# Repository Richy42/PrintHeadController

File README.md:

# PrintHeadController
A 3D printer controller board

Inspired by the possibility of Klipper 3D printer firmware (https://www.klipper3d.org/ ) that allows to have several I/O controller boards, PrintHeadController is a small board intended to be mounted on the moving print head assembly.

This reduces the cabling effort significantly as only power supply and USB is needed.

PrintHeadController has the following features:
* Based on the RP2040 MCU (the one that is used on the Raspberry PI Pico), so it is supported by the Klipper firmware out of the box
* Single socket for a stepper driver module e.g. DRV8825, various TMC variants
* Supports the SPI configuration of TMC drivers
* 12 V and 24 V capable
* 4 Digital inputs
* 4 MOSFET outputs (e.g. hotend heater, fans)
* 4 Thermistor inputs
* BLTouch support
* Debug pins accessible
* Accelerometer ADXL245 optional on board

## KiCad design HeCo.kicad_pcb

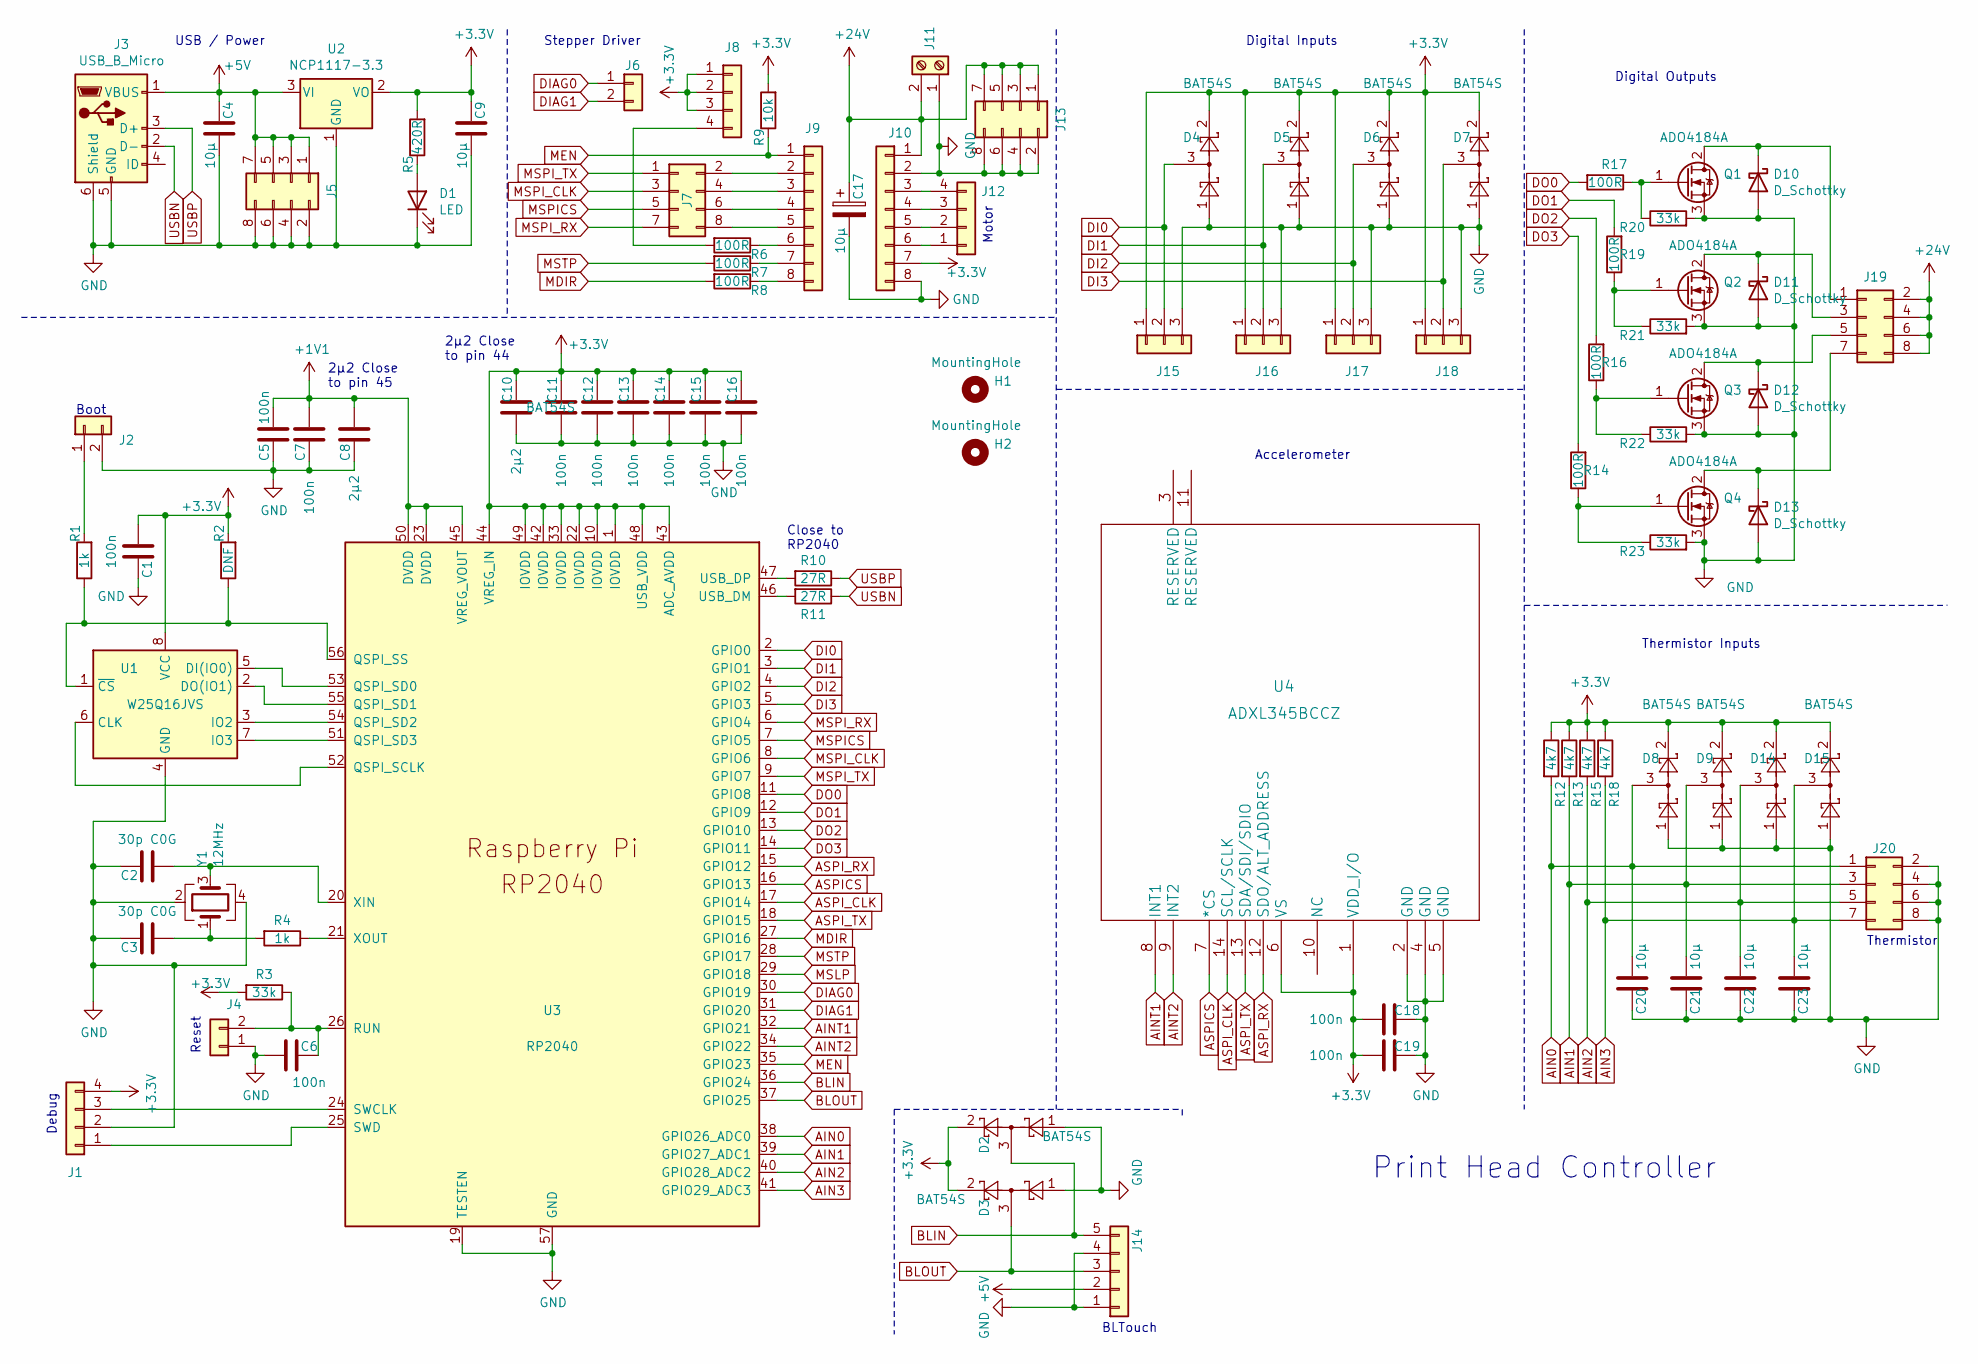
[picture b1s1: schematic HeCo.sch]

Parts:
C1, C5, C6, C7, C11, C12, C13, C14, C15, C16, C18, C19: 100n; C_0603_1608Metric
C2, C3: 30p C0G; C_0603_1608Metric
C4, C9, C20, C21, C22, C23: 10µ; C_0603_1608Metric
C8, C10: 2µ2; C_0603_1608Metric
C17: 10µ; CP_Elec_4x3
D1: LED; LED_0603_1608Metric
D2, D3, D4, D5, D6, D7, D8, D9, D14, D15: BAT54S; SOT-23
D10, D11, D12, D13: D_Schottky; D_0603_1608Metric
H1, H2: MountingHole; MountingHole_3.2mm_M3
J1, J8, J12: Conn_01x04; PinHeader_1x04_P2.54mm_Vertical
J2, J4: Conn_01x02; PinHeader_1x02_P2.54mm_Vertical
J3: USB_B_Micro; USB_Micro-B_Molex_47346-0001
J5, J7, J13, J19, J20: Conn_02x04_Odd_Even; PinHeader_2x04_P2.54mm_Vertical
J6: Conn_01x02; PinSocket_1x02_P2.54mm_Vertical
J9, J10: Conn_01x08; PinSocket_1x08_P2.54mm_Vertical
J11: Screw_Terminal_01x02; PhoenixContact_MSTBVA_2,5_2-G-5,08_1x02_P5.08mm_Vertical
J14: Conn_01x05; PinHeader_1x05_P2.54mm_Vertical
J15, J16, J17, J18: Conn_01x03; PinHeader_1x03_P2.54mm_Vertical
Q1, Q2, Q3, Q4: ADO4184A; TO-252-2
R1, R4: 1k; R_0603_1608Metric
R2: DNF; R_0603_1608Metric
R3, R20, R21, R22, R23: 33k; R_0603_1608Metric
R5: 420R; R_0603_1608Metric
R6, R7, R8, R14, R16, R17, R19: 100R; R_0603_1608Metric
R9: 10k; R_0603_1608Metric
R10, R11: 27R; R_0603_1608Metric
R12, R13, R15, R18: 4k7; R_0603_1608Metric
U1: W25Q16JVS; SOIC-8_5.23x5.23mm_P1.27mm
U2: NCP1117-3.3; SOT-223-3_TabPin2
U3: RP2040; RP2040-QFN-56
U4: ADXL345BCCZ
Y1: 12MHz; Crystal_SMD_3225-4Pin_3.2x2.5mm

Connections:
+1V1: C5.1, C7.1, C8.1, U3.23 (DVDD), U3.45 (VREG_VOUT), U3.50 (DVDD)
+3V3: C1.1, C9.1, C10.1, C11.1, C12.1, C13.1, C14.1, C15.1, C16.1, C18.2, C19.2, D2.2, D3.2, D4.2, D5.2, D6.2, D7.2, D8.2, D9.2, D14.2, D15.2, J1.4, J8.1, J8.2, J8.3, J10.7, J15.1, J16.1, J17.1, J18.1, R2.2, R3.2, R5.2, R9.2, R12.1, R13.1, R15.1, R18.1, U1.8 (VCC), U2.2 (VO), U3.1 (IOVDD), U3.10 (IOVDD), U3.22 (IOVDD), U3.33 (IOVDD), U3.42 (IOVDD), U3.43 (ADC_AVDD), U3.44 (VREG_IN), U3.48 (USB_VDD), U3.49 (IOVDD), U4.1 (VDD_I/O), U4.6 (VS)
+5V: C4.1, J3.1 (VBUS), J5.1, J5.3, J5.5, J5.7, J14.2, U2.3 (VI)
+24V: C17.1, J10.1, J11.2, J13.1, J13.3, J13.5, J13.7, J19.2, J19.4, J19.6, J19.8
AIN0: C20.1, D8.3, J20.1, R12.2, U3.38 (GPIO26_ADC0)
AIN1: C21.1, D9.3, J20.3, R13.2, U3.39 (GPIO27_ADC1)
AIN2: C22.1, D14.3, J20.5, R15.2, U3.40 (GPIO28_ADC2)
AIN3: C23.1, D15.3, J20.7, R18.2, U3.41 (GPIO29_ADC3)
AINT1: U3.32 (GPIO21), U4.8 (INT1)
AINT2: U3.34 (GPIO22), U4.9 (INT2)
ASPICS: U3.16 (GPIO13), U4.7 (*CS)
ASPI_CLK: U3.17 (GPIO14), U4.14 (SCL/SCLK)
ASPI_RX: U3.15 (GPIO12), U4.12 (SDO/ALT_ADDRESS)
ASPI_TX: U3.18 (GPIO15), U4.13 (SDA/SDI/SDIO)
BLIN: D2.3, J14.5, U3.36 (GPIO24)
BLOUT: D3.3, J14.3, U3.37 (GPIO25)
DI0: D4.3, J15.2, U3.2 (GPIO0)
DI1: D5.3, J16.2, U3.3 (GPIO1)
DI2: D6.3, J17.2, U3.4 (GPIO2)
DI3: D7.3, J18.2, U3.5 (GPIO3)
DIAG0: J6.1, U3.30 (GPIO19)
DIAG1: J6.2, U3.31 (GPIO20)
DO0: R17.2, U3.11 (GPIO8)
DO1: R19.2, U3.12 (GPIO9)
DO2: R16.2, U3.13 (GPIO10)
DO3: R14.2, U3.14 (GPIO11)
GND: C1.2, C2.2, C3.2, C4.2, C5.2, C6.2, C7.2, C8.2, C9.2, C10.2, C11.2, C12.2, C13.2, C14.2, C15.2, C16.2, C17.2, C18.1, C19.1, C20.2, C21.2, C22.2, C23.2, D1.1 (K), D2.1, D3.1, D4.1, D5.1, D6.1, D7.1, D8.1, D9.1, D10.2 (A), D11.2 (A), D12.2 (A), D13.2 (A), D14.1, D15.1, J1.2, J2.2, J3.5 (GND), J3.6 (Shield), J4.1, J5.2, J5.4, J5.6, J5.8, J10.2, J10.8, J11.1, J13.2, J13.4, J13.6, J13.8, J14.1, J14.4, J15.3, J16.3, J17.3, J18.3, J20.2, J20.4, J20.6, J20.8, Q1.3 (S), Q2.3 (S), Q3.3 (S), Q4.3 (S), R20.2, R21.2, R22.2, R23.2, U1.4 (GND), U2.1 (GND), U3.19 (TESTEN), U3.57 (GND), U4.2 (GND), U4.4 (GND), U4.5 (GND), Y1.2, Y1.4
MDIR: R8.2, U3.27 (GPIO16)
MEN: J9.1, R9.1, U3.35 (GPIO23)
MSPICS: J7.5, U3.7 (GPIO5)
MSPI_CLK: J7.3, U3.8 (GPIO6)
MSPI_RX: J7.7, U3.6 (GPIO4)
MSPI_TX: J7.1, U3.9 (GPIO7)
MSTP: R7.2, U3.28 (GPIO17)
unnamed: C2.1, U3.20 (XIN), Y1.3
unnamed: C3.1, R4.2, Y1.1
unnamed: C6.1, J4.2, R3.1, U3.26 (RUN)
unnamed: D1.2 (A), R5.1
unnamed: D10.1 (K), J19.1, Q1.2 (D)
unnamed: D11.1 (K), J19.3, Q2.2 (D)
unnamed: D12.1 (K), J19.5, Q3.2 (D)
unnamed: D13.1 (K), J19.7, Q4.2 (D)
unnamed: J1.1, U3.25 (SWD)
unnamed: J1.3, U3.24 (SWCLK)
unnamed: J2.1, R1.2
unnamed: J7.2, J9.2
unnamed: J7.4, J9.3
unnamed: J7.6, J9.4
unnamed: J7.8, J9.5
unnamed: J9.6, R6.1
unnamed: J9.7, R7.1
unnamed: J9.8, R8.1
unnamed: J10.3, J12.4
unnamed: J10.4, J12.3
unnamed: J10.5, J12.2
unnamed: J10.6, J12.1
unnamed: Q1.1 (G), R17.1, R20.1
unnamed: Q2.1 (G), R19.1, R21.1
unnamed: Q3.1 (G), R16.1, R22.1
unnamed: Q4.1 (G), R14.1, R23.1
unnamed: R1.1, R2.1, U1.1 (~CS), U3.56 (QSPI_SS)
unnamed: R4.1, U3.21 (XOUT)
unnamed: R10.2, U3.47 (USB_DP)
unnamed: R11.2, U3.46 (USB_DM)
unnamed: U1.2 (DO(IO1)), U3.55 (QSPI_SD1)
unnamed: U1.3 (IO2), U3.54 (QSPI_SD2)
unnamed: U1.5 (DI(IO0)), U3.53 (QSPI_SD0)
unnamed: U1.6 (CLK), U3.52 (QSPI_SCLK)
unnamed: U1.7 (IO3), U3.51 (QSPI_SD3)
USBN: J3.2 (D-), R11.1
USBP: J3.3 (D+), R10.1

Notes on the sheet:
2µ2 Close to pin 45
Close to RP2040
Boot
Debug
Thermistor
Thermistor Inputs
Digital Outputs
Digital Inputs
USB / Power
Stepper Driver
Accelerometer
BLTouch
Motor
Reset
Print Head Controller
2µ2 Close to pin 44

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
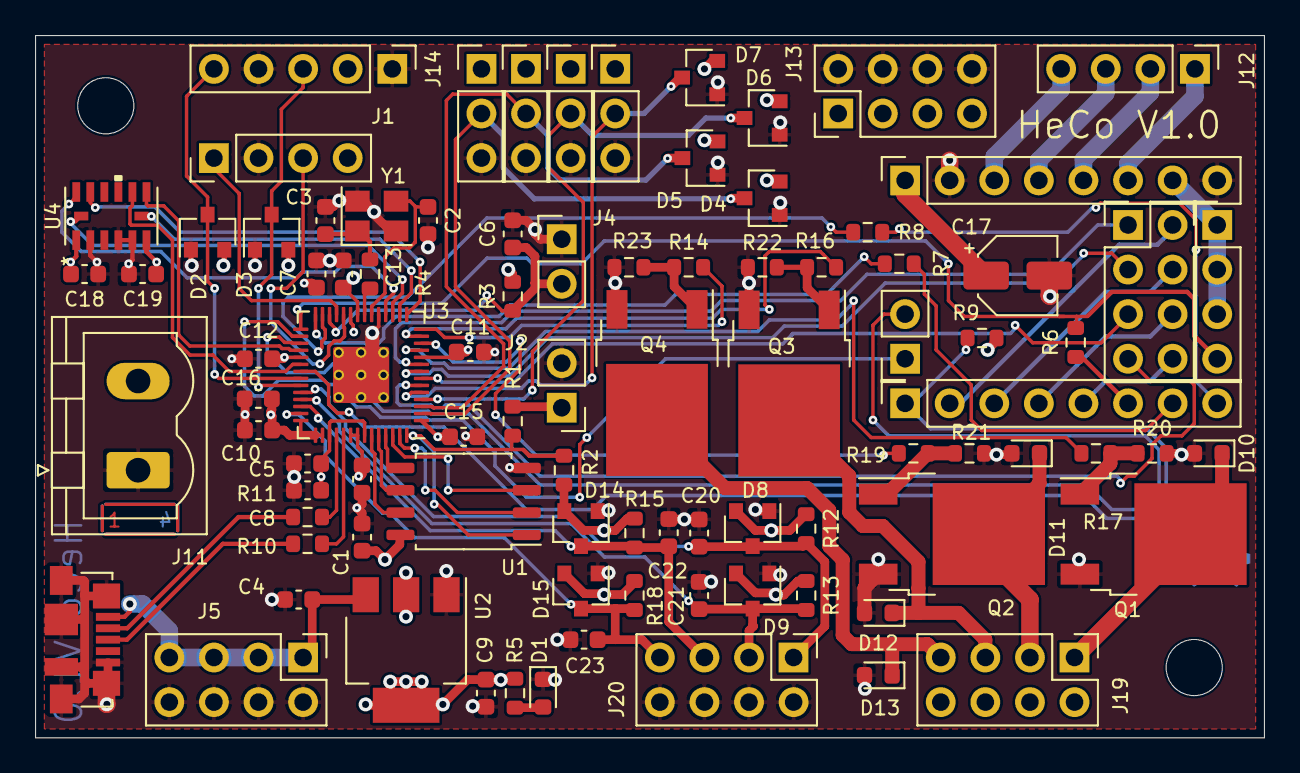
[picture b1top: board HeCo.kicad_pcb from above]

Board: 4 copper layers, 70.0 x 40.0 mm, 92 parts (0 on the bottom side), 72 nets.

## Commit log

2021-11-11 pad overlaping silkscreen corrected
2021-11-13 cleanup / manufacturing files created
2021-11-13 Schematics pdf updated / config prepared
2021-11-13 initial configuration
2021-12-26 silk screen update

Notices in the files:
parts and their libraries:
Copyright 2021 Accelerated Designs. All rights reserved.
